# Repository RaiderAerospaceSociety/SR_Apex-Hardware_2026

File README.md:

# Hardware

This hardware project has four stackable PCBs—Power, Control, Sensor, and Telemetry—connected through pin headers.
These PCBS are actually connected with ribbon cables

## Folder structure

- `boards/` — Design files for the four PCBs.
- `shared/` — Hardware files used by multiple boards.
- `system/` — System-level design and documentation, including board connections.
- `manufacturing/` — Files for PCB fabrication and assembly.
- `tools/` — Hardware-related scripts and utilities.

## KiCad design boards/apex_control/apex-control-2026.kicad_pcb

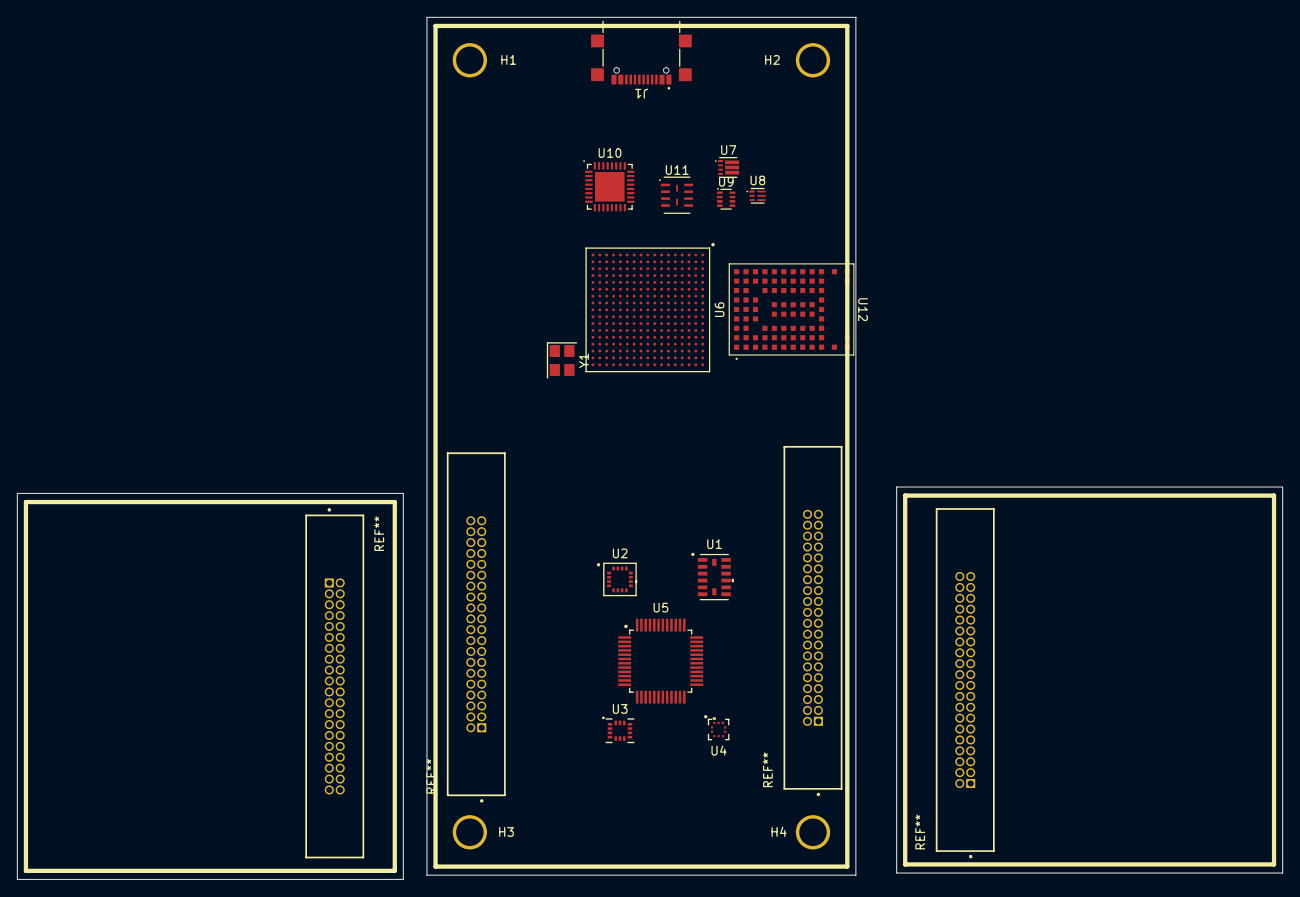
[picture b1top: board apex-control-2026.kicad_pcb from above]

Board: 4 copper layers, 147.5 x 100.5 mm, 18 parts (0 on the bottom side), 44 nets, no tracks yet.

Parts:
H1, H2, H3, H4: M3 MH w/Pad; MH_M3-Pad
J1: UJ20-C-H-G-SMT-5-P16; UJ20-C-H-G-SMT-5-P16_SameSky
U1: ADXL375; ADXL375_LGA_CC-14-1_ADI
U2: MMC5983MA; MMC5983MA_MEM
U3: ICM-45686; ICM-45686_LGA14L_TDK
U4: BMP581; BMP581_QFN10_BOS
U5: RTMC-G2-4IQ48; RTMC-G2-4IQ48_LQFP-48_ThetaMachines
U6: MIMXRT1171DVMAB; MIMXRT1171DVMAB_BGA
U7: TPS62086; TPS62086_RLT0007A_TI
U8: TPS62825; TPS62825_DMQ0006A_TI
U9: LM66200; LM66200_DRL0008A_TI
U10: MKL26Z128VFM4; MKL26Z128VFM4_QFN32_NXP
U11: W25Q64JW; W25Q64JW_USON8_Winbond
U12: MAYA-W166-00B; MAYA-W166_LGA86_u-blox
Y1: Crystal_GND24; XTAL_3225

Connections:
+1V8: U6.D12 (NVCC_DISP1), U6.D14 (NVCC_SD1), U6.E7 (NVCC_DISP2), U6.F6 (NVCC_EMC1), U6.F7 (NVCC_EMC1), U6.G6 (NVCC_EMC1), U6.G13 (NVCC_SD2), U6.G16 (ADC_VREFH), U6.P7 (NVCC_LPSR)
+3V3_1: U6.G12 (VDD_USB_3P3), U6.H6 (NVCC_EMC2), U6.J6 (NVCC_EMC2), U6.J13 (VDDA_ADC_3P3), U6.M12 (NVCC_GPIO), U6.R12 (VDD_LPSR_IN), U7.3 (FB), U7.4 (VOS)
+5V: U7.1 (EN), U7.7 (VIN)
GND: H1.1 (Pad_1), H2.1 (Pad_1), H3.1 (Pad_1), H4.1 (Pad_1), U5.6 (GND), U5.14 (GND), U5.19 (GND), U5.27 (GND), U5.35 (GND), U5.45 (GND), U7.5 (GND), Y1.1, Y1.3
unnamed: U6.M7 (DCDC_ANA), U6.M8 (DCDC_ANA)
unnamed: U6.K8 (DCDC_DIG), U6.K9 (DCDC_DIG), U6.L8 (DCDC_DIG)
unnamed: U6.K6 (DCDC_GND), U6.K7 (DCDC_GND), U6.L6 (DCDC_GND)
unnamed: U6.M5 (DCDC_IN), U6.N5 (DCDC_IN)
unnamed: U6.T4 (DCDC_LN), U6.U4 (DCDC_LN)
unnamed: U6.T3 (DCDC_LP), U6.U3 (DCDC_LP)
unnamed: U6.H8 (VDD_SOC_IN), U6.H9 (VDD_SOC_IN), U6.H10 (VDD_SOC_IN), U6.J8 (VDD_SOC_IN), U6.J9 (VDD_SOC_IN), U6.J10 (VDD_SOC_IN), U6.K10 (VDD_SOC_IN)
unnamed: U6.A1 (VSS), U6.A17 (VSS), U6.B7 (VSS), U6.C8 (VSS), U6.C10 (VSS), U6.C12 (VSS), U6.C14 (VSS), U6.D4 (VSS), U6.F11 (VSS), U6.F12 (VSS), U6.F13 (VSS), U6.G3 (VSS), U6.G7 (VSS), U6.G8 (VSS), U6.G9 (VSS), U6.G10 (VSS), U6.G11 (VSS), U6.G15 (VSS), U6.H7 (VSS), U6.H11 (VSS), U6.J7 (VSS), U6.J11 (VSS), U6.K11 (VSS), U6.L3 (VSS), U6.L10 (VSS), U6.L11 (VSS), U6.L15 (VSS), U6.P4 (VSS), U6.P14 (VSS), U6.R4 (VSS), U6.R7 (VSS), U6.T12 (VSS), U6.U1 (VSS), U6.U17 (VSS)
unnamed: U6.U16 (XTALI), Y1.4 (GND)
unnamed: U6.T16 (XTALO), Y1.2 (GND)
unnamed: U6.T10 (POR_B), U10.22 (PTC1)
unnamed: U6.U8 (GPIO_LPSR_08), U10.24 (PTC3)
unnamed: U6.P5 (GPIO_LPSR_09), U10.25 (PTC4)
unnamed: U6.T6 (GPIO_LPSR_14), U10.26 (PTC5)
unnamed: U6.U7 (GPIO_LPSR_15), U10.27 (PTC6)
unnamed: U6.P6 (GPIO_LPSR_02), U10.32 (PTD7)
unnamed: U6.T7 (GPIO_LPSR_03), U10.1 (PTE0)
unnamed: J1.A6 (D+), J1.B6 (D+), U10.4 (USB0_DM)
unnamed: J1.A7 (D-), J1.B7 (D-), U10.3 (USB0_DP)
unnamed: U10.2 (VSS), U10.16 (VSS)
unnamed: U12.A7 (3V3), U12.B7 (3V3)
unnamed: U6.A7 (GPIO_DISP_B2_14), U12.J9 (BT_DEV_WAKE)
unnamed: U6.A16 (GPIO_SD_B1_05), U12.J7 (BT_RESET)
unnamed: U6.B16 (GPIO_SD_B1_00), U12.E7 (BT_WAKE_HOST)
unnamed: U12.A1 (GND), U12.A9 (GND), U12.B2 (GND), U12.B8 (GND), U12.E4 (GND), U12.E5 (GND), U12.F4 (GND), U12.F5 (GND), U12.H4 (GND), U12.H5 (GND), U12.K2 (GND), U12.K3 (GND), U12.K4 (GND), U12.K6 (GND), U12.K7 (GND), U12.K8 (GND), U12.L1 (GND), U12.L9 (GND), U12.M1 (GND), U12.M2 (GND), U12.M8 (GND), U12.M9 (GND)
unnamed: U6.A3 (GPIO_EMC_B1_09), U12.J3 (PDn)
unnamed: U6.F14 (GPIO_SD_B2_04), U12.A4 (SD_CLK)
unnamed: U6.E14 (GPIO_SD_B2_05), U12.B4 (SD_CMD)
unnamed: U6.E15 (GPIO_SD_B2_03), U12.B3 (SD_DAT[0])
unnamed: U6.H13 (GPIO_SD_B2_02), U12.A3 (SD_DAT[1])
unnamed: U6.J14 (GPIO_SD_B2_01), U12.B5 (SD_DAT[2])
unnamed: U6.J15 (GPIO_SD_B2_00), U12.A5 (SD_DAT[3])
unnamed: U6.A5 (GPIO_DISP_B2_13), U12.H8 (UART_CTSn)
unnamed: U6.B6 (GPIO_DISP_B2_12), U12.H9 (UART_RTSn)
unnamed: U6.D9 (GPIO_DISP_B2_10), U12.G8 (UART_SIN)
unnamed: U6.A6 (GPIO_DISP_B2_11), U12.G9 (UART_SOUT)
unnamed: U6.A4 (GPIO_DISP_B2_15), U12.J8 (WLAN_DEV_WAKE)
unnamed: U6.C15 (GPIO_SD_B1_02), U12.H7 (WLAN_RESET)
unnamed: U6.B17 (GPIO_SD_B1_03), U12.F7 (WLAN_WAKE_HOST)
VDD: U5.7 (VDD), U5.15 (VDD), U5.20 (VDD), U5.28 (VDD), U5.36 (VDD), U5.46 (VDD)

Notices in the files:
parts and their libraries:
Theta Machines RTMC-G2-4IQ48 real-time motion controller, LQFP-48 7x7mm P0.5mm (JEDEC MS-026 BBC). Copper kept from DEV-G2-NANO RTMC-G2-4IQ48 footprint (Theta Machines, CERN-OHL-P); no public manufacturer land pattern
